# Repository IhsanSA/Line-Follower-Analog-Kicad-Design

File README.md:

An Analog Line Follower Robot is a mobile robot designed to follow a predefined path—usually a black line on a white surface or the reverse—by using analog electronic signals rather than digital processing with a microcontroller. This type of robot is widely used in education because it clearly demonstrates the fundamentals of analog electronics and basic control systems.

Working Principle

The robot operates using light-based sensors, most commonly Light Dependent Resistors (LDRs) or infrared (IR) sensors. White surfaces reflect more light, while black lines absorb more light.

This difference in reflected light produces varying analog voltage levels at the sensor output. These voltages are then processed directly or compared using a comparator circuit. Based on the difference between the left and right sensors, the robot adjusts the speed of its motors. If the robot starts drifting off the line, one motor slows down or stops, causing the robot to steer back onto the path.

There is no programming involved. The robot’s behavior emerges purely from the interaction between sensors, electrical signals, and motors.

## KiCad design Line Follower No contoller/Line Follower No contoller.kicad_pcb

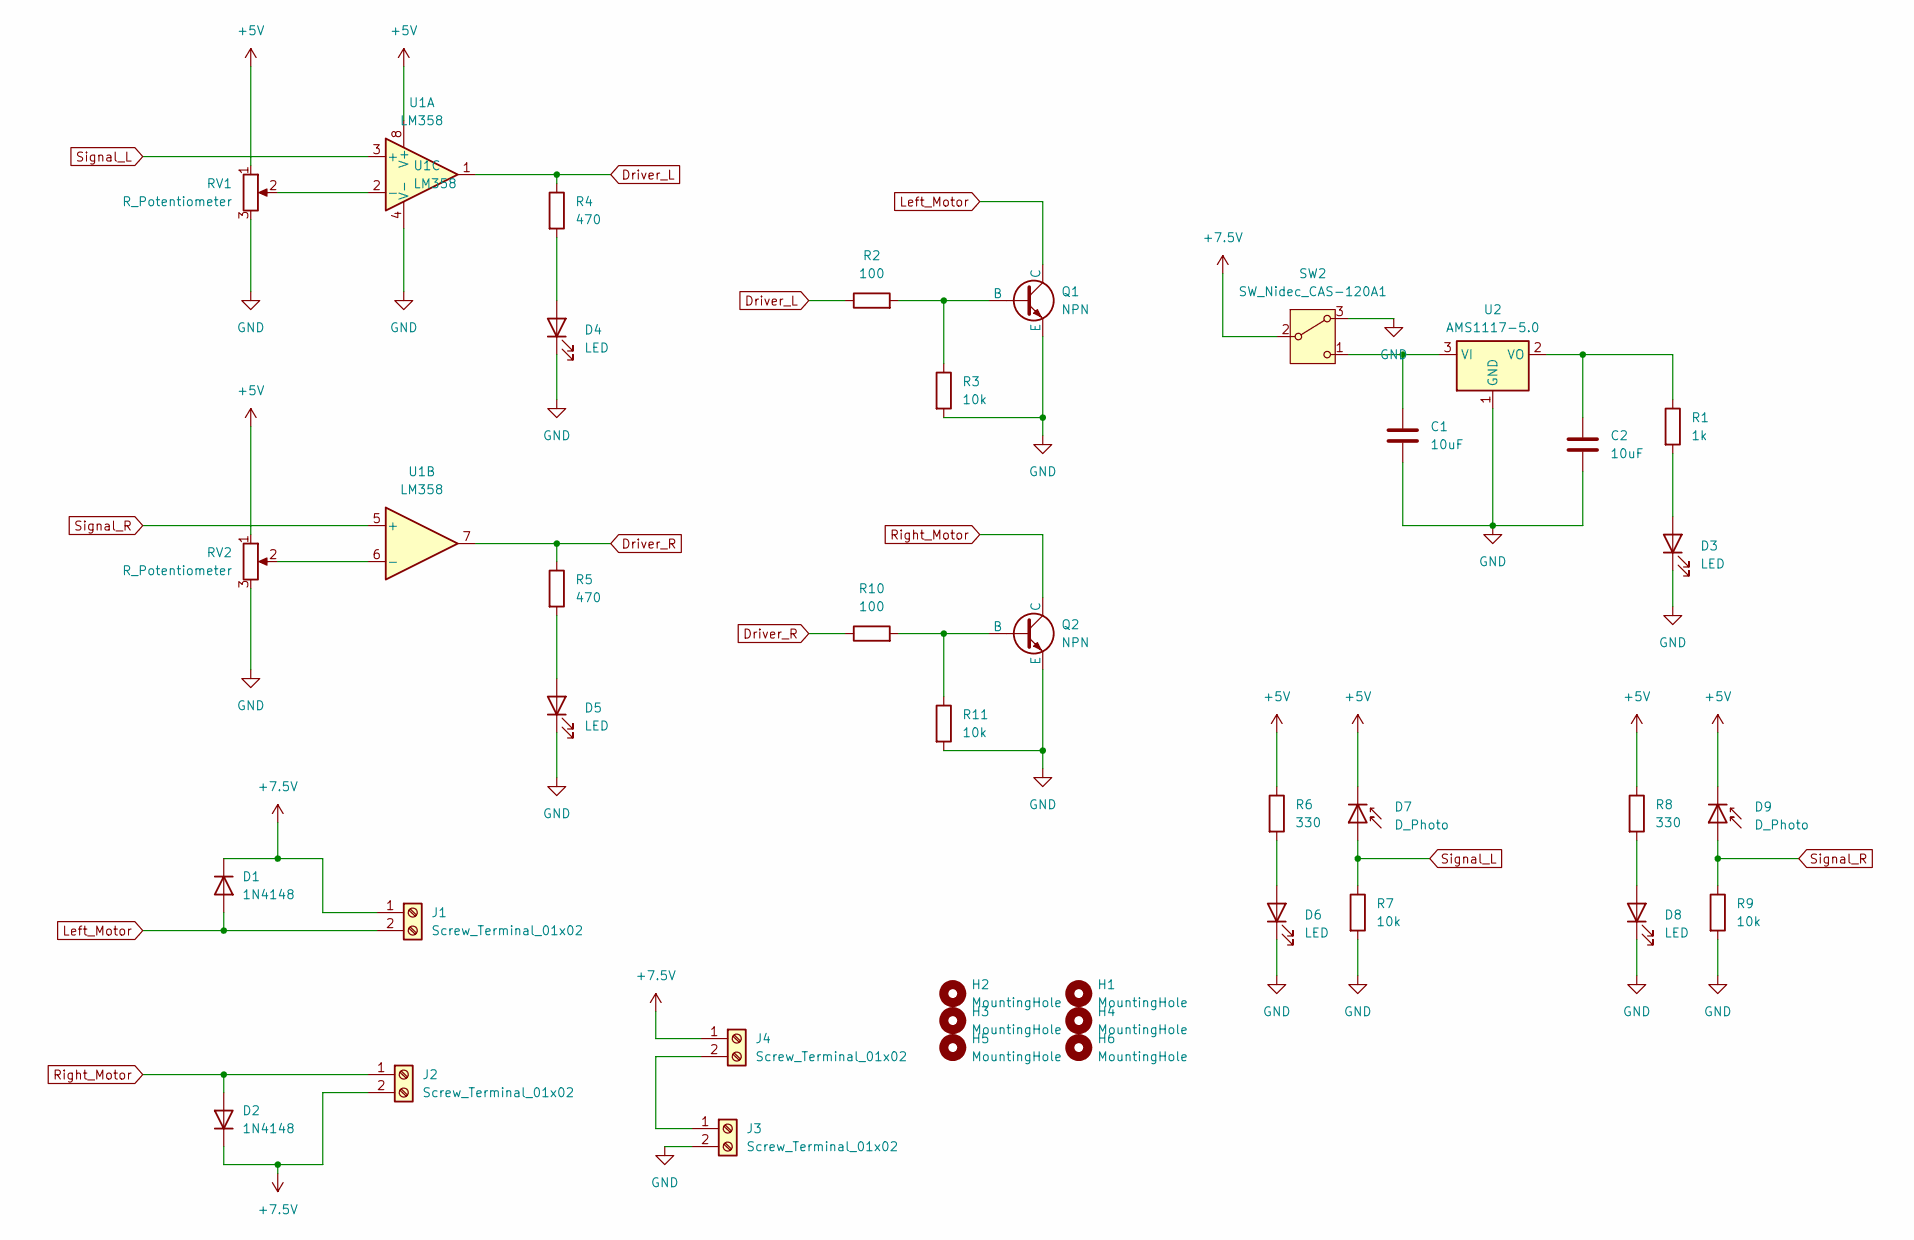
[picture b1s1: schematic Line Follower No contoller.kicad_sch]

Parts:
C1, C2: 10uF; C_1808_4520Metric_Pad1.72x2.30mm_HandSolder
D1, D2: 1N4148; D_DO-35_SOD27_P7.62mm_Horizontal
D3, D4, D5, D6, D8: LED; LED_D3.0mm_IRBlack
D7, D9: D_Photo; D_A-405_P7.62mm_Horizontal
H1, H2, H3, H4, H5, H6: MountingHole; MountingHole_2.1mm
J1, J2, J3, J4: Screw_Terminal_01x02; TerminalBlock_4Ucon_1x02_P3.50mm_Vertical
Q1, Q2: NPN; TO-92_Inline_Wide
R1: 1k; R_Axial_DIN0204_L3.6mm_D1.6mm_P7.62mm_Horizontal
R2, R10: 100; R_Axial_DIN0204_L3.6mm_D1.6mm_P7.62mm_Horizontal
R3, R7, R9, R11: 10k; R_Axial_DIN0204_L3.6mm_D1.6mm_P7.62mm_Horizontal
R4, R5: 470; R_Axial_DIN0204_L3.6mm_D1.6mm_P7.62mm_Horizontal
R6, R8: 330; R_Axial_DIN0204_L3.6mm_D1.6mm_P7.62mm_Horizontal
RV1, RV2: R_Potentiometer; Potentiometer_Piher_PT-10-H01_Horizontal
SW2: SW_Nidec_CAS-120A1; Nidec_Copal_CAS-120A
U1: LM358; DIP-8_W7.62mm_SMDSocket_SmallPads
U2: AMS1117-5.0; SOT-223-3_TabPin2

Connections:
+5V: D7.1 (K), D9.1 (K), R6.1, R8.1, RV1.1, RV2.1, U1.8 (V+)
+7.5V: D1.1 (K), D2.1 (K), J1.1, J2.2, J4.1, SW2.2 (B)
Driver_L: R2.1, R4.1, U1.1
Driver_R: R5.1, R10.1, U1.7
GND: C1.2, C2.2, D3.1 (K), D4.1 (K), D5.1 (K), D6.1 (K), D8.1 (K), J3.2, Q1.3 (E), Q2.3 (E), R3.2, R7.2, R9.2, R11.2, RV1.3, RV2.3, SW2.3 (A), U1.4 (V-), U2.1 (GND)
Left_Motor: D1.2 (A), J1.2, Q1.1 (C)
unnamed: D3.2 (A), R1.2
unnamed: D4.2 (A), R4.2
unnamed: D5.2 (A), R5.2
unnamed: D6.2 (A), R6.2
unnamed: D8.2 (A), R8.2
unnamed: J3.1, J4.2
unnamed: Q1.2 (B), R2.2, R3.1
unnamed: Q2.2 (B), R10.2, R11.1
unnamed: C1.1, SW2.1 (C), U2.3 (VI)
unnamed: RV1.2, U1.2 (-)
unnamed: RV2.2, U1.6 (-)
unnamed: C2.1, R1.1, U2.2 (VO)
Right_Motor: D2.2 (A), J2.1, Q2.1 (C)
Signal_L: D7.2 (A), R7.1, U1.3 (+)
Signal_R: D9.2 (A), R9.1, U1.5 (+)

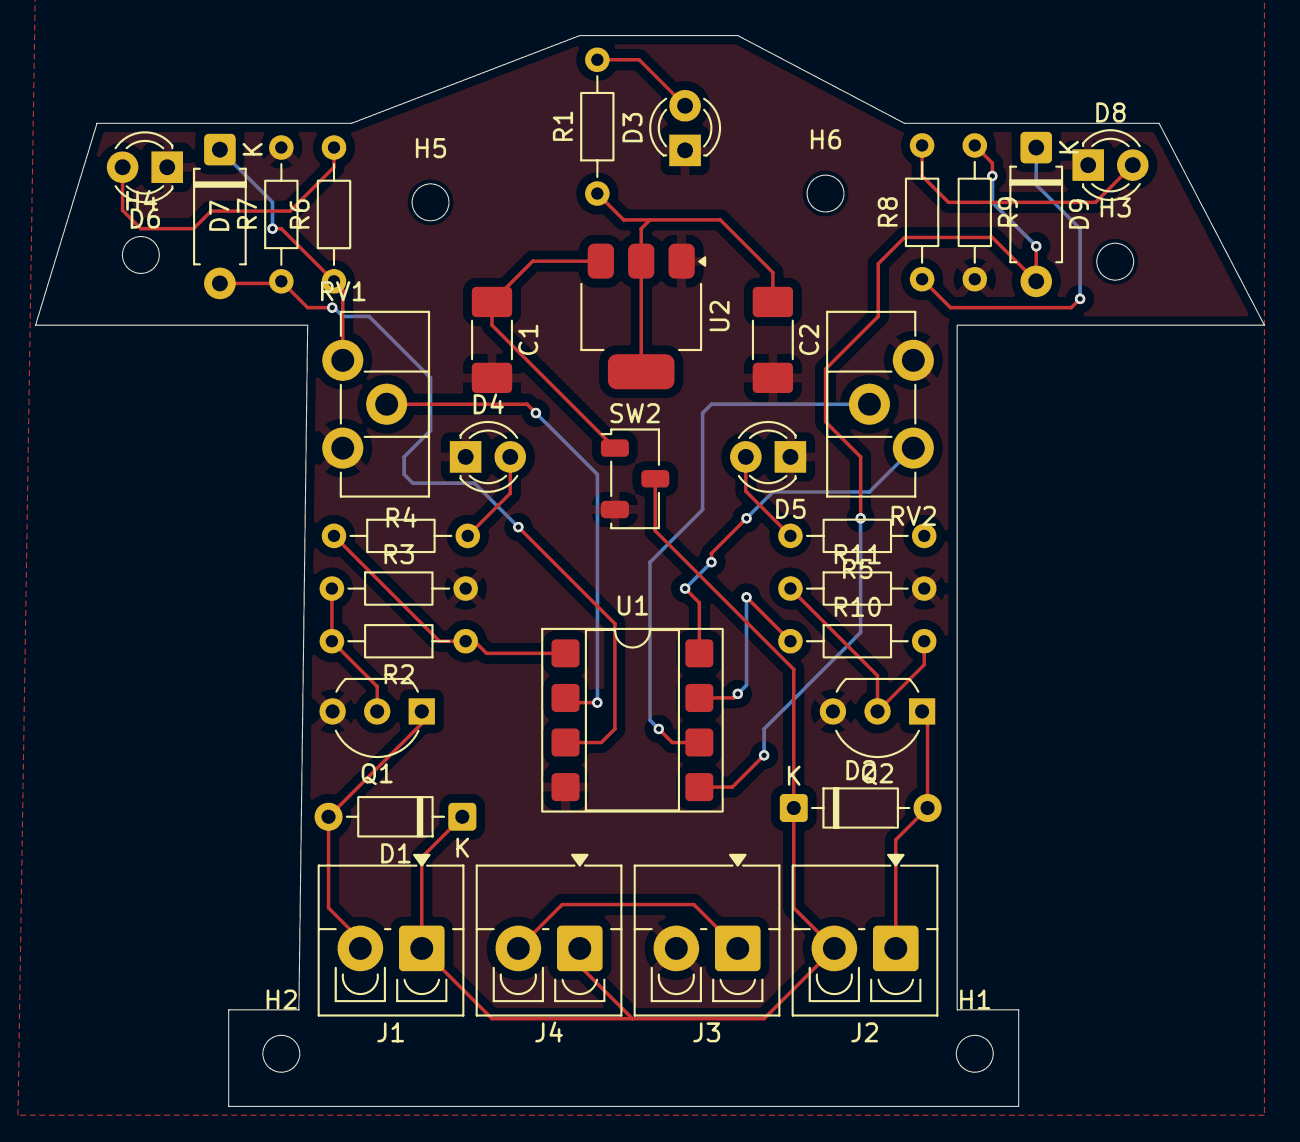
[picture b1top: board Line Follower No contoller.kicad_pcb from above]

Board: 2 copper layers, 70.0 x 61.0 mm, 39 parts (0 on the bottom side), 21 nets.

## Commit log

2026-01-05 Create Description
    An analog line follower robot is a type of mobile robot designed to move automatically by following a visible line on the floor. The line is usually black on a white surface or white on a dark surfac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
2026-01-05 Add files via upload
    Designing Robot Line Follower with Kicad
